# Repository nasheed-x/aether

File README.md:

# Aether: Flight Computer

## Overview

Aether is a multifunctional flight computer designed as an adaptable testbed for a variety of flight hardware and software components. The primary objective of this project is to evaluate external sensors and various algorithmic approaches, with a specific focus on sensor fusion techniques. These techniques aim to extract essential data regarding the rocket's states throughout its flight. The flight computer is equipped with the capability to interface with on-board rocket hardware, including deployment mechanisms.

## Key Features

- **Sensor Evaluation:** Aether serves as a platform for evaluating external sensors, with a particular emphasis on sensor fusion techniques.

- **Algorithmic Exploration:** The project explores various algorithmic approaches to extract crucial data about the rocket's states during its flight.

- **Hardware Interface:** The flight computer is designed to interface seamlessly with on-board rocket hardware, facilitating communication and control, especially with deployment mechanisms.

- **Dual Microcontroller Units:** Aether incorporates two microcontroller units (MCUs), each specialized for distinct tasks. One MCU is dedicated to data sampling, while the other focuses on communication with the ground station.

## Microcontrollers on Board

| Microcontroller         |
|-------------------------|
| STM32F405RGTx           |
| ESP32-S3-MINI-1U-N8     |

## Components on Board

| Component                                         | Interface |
|------------------------------------------------|-----------|
| TE MS8607 PHT Sensor                           | I2C       |
| DPS310 Precision Barometric Pressure and Altitude Sensor | I2C, SPI  |
| H3LIS331 Ultra High Range Triple-Axis Accelerometer | I2C, SPI  |
| LSM6DSO32 6-DoF Accelerometer and Gyroscope    | I2C, SPI  |
| Sensirion SHT45 Precision Temperature & Humidity Sensor | I2C       |
| SAM M10Q (GPS)                                       | I2C       |
| RFM 95 HCW (LoRa Transceiver)                                | SPI       |
| W25Q128JVSIQ (Flash)                           | SPI       |

## Project Link

View this project on [CADLAB.io](https://cadlab.io/project/27167) for additional details, documentation, and collaborative contributions.

Feel free to explore, contribute, and adapt Aether as needed for your specific flight hardware and software requirements.

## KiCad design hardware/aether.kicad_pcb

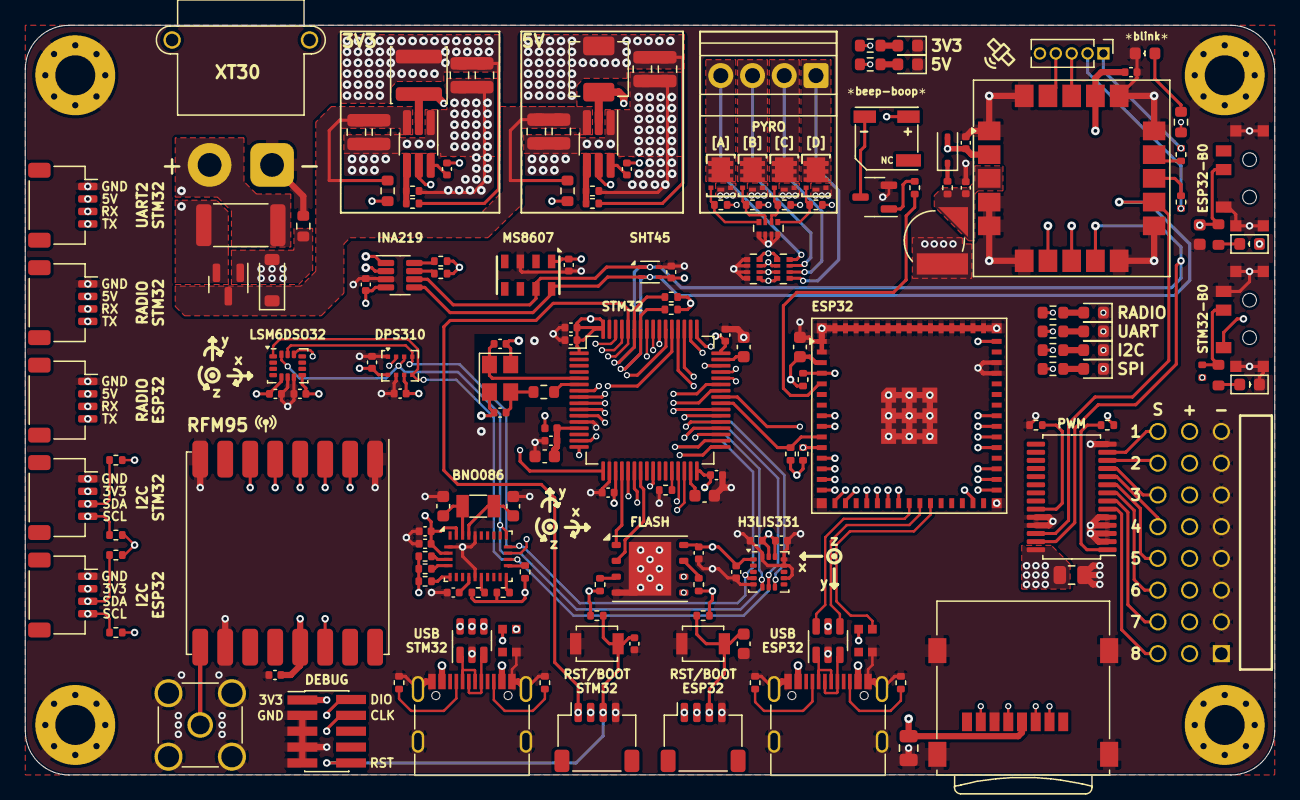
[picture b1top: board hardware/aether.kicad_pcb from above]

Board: 6 copper layers, 100.0 x 60.0 mm, 173 parts (0 on the bottom side), 147 nets.

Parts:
ANT1: Antenna_Shield; SMA_Amphenol_901-144_Vertical
BT1: Battery_Cell; SEIKO_ML414H_IV01E
BUZ1: FST-5030; BUZ-SMD_FST-5030
C1, C2: 2.2uF; C_0603_1608Metric
C3, C4, C5, C6, C7, C10, C12, C16, C17, C18, C19, C20, C21, C22, C23, C24, C26, C27, C28, C30, C31, C34, C39, C42, C43, C46, C47: 100nF; C_0402_1005Metric
C8, C9: 10pF; C_0402_1005Metric
C11, C13, C14: 1uF; C_0603_1608Metric
C15: 10uF; C_0603_1608Metric
C25, C29, C32, C33, C37, C38: 10uF; C_0805_2012Metric
C35, C36, C40, C41: 22uF; C_0805_2012Metric
C44, C45: 22pF; C_0603_1608Metric
D1: PULSE_LED; LED_0603_1608Metric
D2: 0.5A/40V/420mV; D_SOD-323
D3: FUXINSEMI DSK34; D_SOD-123
D4: RUBY RED; LED_0603_1608Metric
D5: ROYAL BLUE; LED_0603_1608Metric
D6: EMERALD GREEN; LED_0603_1608Metric
D7: ORANGE; LED_0603_1608Metric
ESP32-S3: ESP32-S3-MINI-1U; ESP32-S2-MINI-1U
ESPBOOT0: G; LED_0603_1608Metric
ESPRGB1: WS2812B-2020; LED_WS2812B-2020_PLCC4_2.0x2.0mm
ESP_B0: SS-3292S-L2-B; SW-SMD_SS-3292S-L2-B
ESP_RST1: SW_Push; SW_SPST_B3U-1000P
FB1: 600Ω; L_0402_1005Metric
G2: LOGO
GPS_IO1: Conn_01x05_Pin; PinHeader_1x05_P1.27mm_Vertical
H1, H2, H3, H4: MountingHole_Pad; MountingHole_3.2mm_M3_Pad_Via
HSE1: 25MHz; Crystal_SMD_Abracon_ABM8G-4Pin_3.2x2.5mm
I2C-ESP1, I2C-STM1: SM04B-SRSS-TB(LF)(SN); JST_SH_SM04B-SRSS-TB_1x04-1MP_P1.00mm_Horizontal
INA219: INA219AxDCN; SOT-23-8
L1: 4.7uH; L_Changjiang_FXL0420
L2: 3.3uH; L_Changjiang_FNR4030S
LED1, LED2: R; LED_0603_1608Metric
PCA9685: PCA9685PW; TSSOP-28_4.4x9.7mm_P0.65mm
PWM1: 24-Pin 8x3 Male Header - Angle; SAMTEC_TSW-108-08-T-T-RA
PYRO1: Screw_Terminal_01x04; TerminalBlock_Xinya_XY308-2.54-4P_1x04_P2.54mm_Horizontal
Q1: S8050_C2146; SOT-23-3
Q6: AO3401A; SOT-23
R1, R5, R13, R25, R26, R27, R28, R29, R30, R31, R32, R37, R40, R42, R43, R58, R59, R60, R61: 10k; R_0402_1005Metric
R2: 180; R_0402_1005Metric
R3: 620; R_0603_1608Metric
R4: 2.2K; R_0603_1608Metric
R6, R7, R16, R19, R20, R55: 5.1k; R_0402_1005Metric
R8, R9, R10, R11: 330; R_0402_1005Metric
R12, R23, R45, R46, R47, R48, R49, R50: 2.2k; R_0603_1608Metric
R14, R15, R33, R34, R56, R57: 4.7k; R_0402_1005Metric
R21, R22: 470; R_0402_1005Metric
R24: 3.3k; R_0402_1005Metric
R35, R38, R41: 100k; R_0603_1608Metric
R36: 54.9k; R_0402_1005Metric
R39: 33.2k; R_0402_1005Metric
R44: 0.01; R_2512_6332Metric
RFM95: RFM95W-915S2; HOPERF_RFM9XW_SMD
RN1: 10k; R_Array_Convex_4x0402
RN2: 47k; R_Array_Convex_4x0402
RN3: 220k; R_Array_Convex_4x0402
RST_BOOT_ESP1: SM04B-SRSS-TB(LF)(SN); JST_SH_SM04B-SRSS-TB_1x04-1MP_P1.00mm_Horizontal
RST_BOOT_STM1: SM04B-SRSS-TB(LF)(SN); JST_SH_SM04B-SRSS-TB_1x04-1MP_P1.00mm_Horizontal
SAM-M10Q1: SAM-M10Q-00B; ublox_SAM-M8Q
SD1: Micro_SD_Card; microSD_HC_Wuerth_693072010801
STM32F4: STM32F405RGTx; LQFP-64_10x10mm_P0.5mm
STMBOOT0: LED; LED_0603_1608Metric
STMRGB1: WS2812B-2020; LED_WS2812B-2020_PLCC4_2.0x2.0mm
STM_B0: SS-3292S-L2-B; SW-SMD_SS-3292S-L2-B
STM_RST1: SW_Push; SW_SPST_B3U-1000P
SWD1: Conn_02x05_Odd_Even; PinHeader_2x05_P1.27mm_Vertical_SMD
U1, U2: USBLC6-2SC6; SOT-23-6
U3, U7, U12, U14: SI5448DU-T1-GE3; SON_8DU-T1-GE3_VIS
U4: DPS310; XDCR_DPS310
U5: H3LIS331DL; LGA-16_3x3mm_P0.5mm_LayoutBorder3x5y
U6: LSM6DSO32TR; LGA-14_3x2.5mm_P0.5mm_LayoutBorder3x4y
U8: MS860702BA01-50; MS8607-02BA01
U9: SHT45-AD1B-R2; Sensirion_DFN-4_1.5x1.5mm_P0.8mm_SHT4x_NoCentralPad
U10, U11: TPS562201DDCR; TSOT-23-6_HandSoldering
U13: BNO086; LGA-28_5.2x3.8mm_P0.5mm
U15: W25Q128JVP; WSON-8-1EP_6x5mm_P1.27mm_EP3.4x4.3mm
UART1-RFD-ESP1, UART1-RFD-STM1, UART2-STM1: SM04B-SRSS-TB(LF)(SN); JST_SH_SM04B-SRSS-TB_1x04-1MP_P1.00mm_Horizontal
USB_ESP32: USB_C_Receptacle_USB2.0; USB_C_Receptacle_G-Switch_GT-USB-7010ASV
USB_STM32: USB_C_Receptacle_USB2.0; USB_C_Receptacle_G-Switch_GT-USB-7010ASV
XT30: XT30PW-M; AMASS_XT30PW-M_1x02_P2.50mm_Horizontal
Y1: 32.768kHz; Crystal_SMD_3215-2Pin_3.2x1.5mm

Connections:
3.3V: BUZ1.1 (+), C3.1, C4.1, C5.1, C6.1, C7.1, C15.1, C16.1, C17.1, C18.1, C19.1, C20.1, C21.1, C22.1, C24.1, C25.1, C26.1, C27.1, C28.1, C29.1, C30.1, C31.1, C40.1, C41.1, C42.1, C46.1, C47.1, D2.2 (A), ESP32-S3.3 (3V3), ESPBOOT0.2 (A), ESPRGB1.4 (VDD), FB1.2, I2C-ESP1.2, I2C-STM1.2, INA219.4 (VS), L2.2, PCA9685.28 (VDD), R13.2, R14.2, R15.2, R16.2, R25.1, R26.1, R28.2, R29.2, R30.2, R31.2, R32.2, R33.2, R34.2, R39.1, R42.2, R43.2, R46.1, R55.2, R56.2, R57.2, R58.1, R59.1, R60.1, R61.2, RFM95.13 (3.3V), RST_BOOT_ESP1.2, RST_BOOT_STM1.2, SAM-M10Q1.2 (V_IO), SAM-M10Q1.17 (VCC), SD1.4 (VDD), STM32F4.1 (VBAT), STM32F4.19 (VDD), STM32F4.32 (VDD), STM32F4.48 (VDD), STM32F4.64 (VDD), STMRGB1.4 (VDD), STM_B0.1, SWD1.1, U4.6 (VDDIO), U4.8 (VDD), U5.1 (VDD_IO), U5.14 (VDD), U5.15 (VDD), U6.5 (VDDIO), U6.8 (VDD), U8.1 (VDD), U9.3 (VDD), U13.3 (VDD), U13.28 (VDDIO), U15.8 (VCC)
5V: C35.1, C36.1, L1.2, PWM1.02, PWM1.05, PWM1.08, PWM1.11, PWM1.14, PWM1.17, PWM1.20, PWM1.23, R36.1, R45.1, UART1-RFD-ESP1.2, UART1-RFD-STM1.2, UART2-STM1.2
BNO086_CS: STM32F4.39 (PC8), U13.18 (~H_CS)
BNO086_MISO: SD1.3 (CMD), STM32F4.35 (PB14), U4.3 (SDI), U5.6 (SDA/SDI/SDO), U6.14 (SDA), U13.20 (H_SDA/H_MISO/TX)
BNO086_MOSI: SD1.7 (DAT0), STM32F4.36 (PB15), U4.5 (SDO), U5.7 (SDO/SA0), U6.1 (SDO/SA0), U13.17 (SA0/H_MOSI)
BNO086_RST: R61.1, U13.11 (~RST)
BNO086_SCK: SD1.5 (CLK), STM32F4.34 (PB13), U4.4 (SCK), U5.4 (SCL/SPC), U6.13 (SCL), U13.19 (H_SCL/SCK/RX)
BUZZ_IN: ESP32-S3.5 (IO1), R2.2
CROSS_I2C: ESP32-S3.36 (IO40), R49.2
CROSS_SPI: ESP32-S3.35 (IO39), R48.2
CROSS_UART: ESP32-S3.37 (IO41), R50.2
DPS310_CSB: STM32F4.33 (PB12), U4.2 (~CSB)
ESP32-EN: C14.1, ESP32-S3.45 (EN), ESP_RST1.2, R16.1, RST_BOOT_ESP1.3
ESP32-GPIO0: C13.1, ESP32-S3.4 (IO0), ESP_B0.2, R12.1, R13.1, RST_BOOT_ESP1.1
ESP32-I2C1_SCL: ESP32-S3.9 (IO5), I2C-ESP1.4, R32.1
ESP32-I2C1_SDA: ESP32-S3.8 (IO4), I2C-ESP1.3, R31.1
ESP32-I2C2_SCL: ESP32-S3.11 (IO7), R15.1, STM32F4.41 (PA8)
ESP32-I2C2_SDA: ESP32-S3.10 (IO6), R14.1, STM32F4.40 (PC9)
ESP32-RGB_IN: ESP32-S3.25 (IO21), ESPRGB1.3 (DIN)
ESP32-RX1: ESP32-S3.22 (IO18), UART1-RFD-ESP1.3
ESP32-RX2: ESP32-S3.20 (IO16), STM32F4.51 (PC10)
ESP32-SPI1_CS0: ESP32-S3.14 (IO10), RFM95.5 (NSS)
ESP32-SPI1_MISO: ESP32-S3.17 (IO13), RFM95.2 (MISO)
ESP32-SPI1_MOSI: ESP32-S3.15 (IO11), RFM95.3 (MOSI)
ESP32-SPI1_SCK: ESP32-S3.16 (IO12), RFM95.4 (SCK)
ESP32-SPI2_CS0: ESP32-S3.29 (IO34), STM32F4.50 (PA15)
ESP32-SPI2_MISO: ESP32-S3.33 (IO37), STM32F4.56 (PB4)
ESP32-SPI2_MOSI: ESP32-S3.31 (IO35), STM32F4.57 (PB5)
ESP32-SPI2_SCK: ESP32-S3.32 (IO36), STM32F4.55 (PB3)
ESP32-TX1: ESP32-S3.21 (IO17), UART1-RFD-ESP1.4
ESP32-TX2: ESP32-S3.19 (IO15), STM32F4.52 (PC11)
ESP32-USB_D+: ESP32-S3.24 (USB_D+), U2.4 (I/O2)
ESP32-USB_D-: ESP32-S3.23 (USB_D-), U2.6 (I/O1)
F405_VDDA: C10.1, C11.1, FB1.1, STM32F4.13 (VDDA)
FLASH_CLK: STM32F4.21 (PA5), U15.6 (CLK)
FLASH_CS: STM32F4.20 (PA4), U15.1 (~CS)
FLASH_HOLD: R26.2, U15.7 (~HOLD/~RESET/IO_{3})
FLASH_SDI: STM32F4.22 (PA6), U15.5 (DI/IO_{0})
FLASH_SDO: STM32F4.23 (PA7), U15.2 (DO/IO_{1})
FLASH_WP: R25.2, U15.3 (~WP/IO_{2})
GND: ANT1.2 (Shield), BT1.2 (-), C1.2, C2.2, C3.2, C4.2, C5.2, C6.2, C7.2, C8.1, C9.2, C10.2, C11.2, C12.2, C13.2, C14.2, C15.2, C16.2, C17.2, C18.2, C19.2, C20.2, C21.2, C22.2, C23.2, C24.2, C25.2, C26.2, C27.2, C28.2, C29.2, C30.2, C31.2, C32.2, C33.2, C35.2, C36.2, C37.2, C38.2, C40.2, C41.2, C42.2, C43.2, C44.2, C45.2, C46.2, C47.2, D1.1 (K), D4.1 (K), D5.1 (K), D6.1 (K), D7.1 (K), ESP32-S3.1 (GND), ESP32-S3.2 (GND), ESP32-S3.42 (GND), ESP32-S3.43 (GND), ESP32-S3.46 (GND), ESP32-S3.47 (GND), ESP32-S3.48 (GND), ESP32-S3.49 (GND), ESP32-S3.50 (GND), ESP32-S3.51 (GND), ESP32-S3.52 (GND), ESP32-S3.53 (GND), ESP32-S3.54 (GND), ESP32-S3.55 (GND), ESP32-S3.56 (GND), ESP32-S3.57 (GND), ESP32-S3.58 (GND), ESP32-S3.59 (GND), ESP32-S3.60 (GND), ESP32-S3.61 (GND), ESP32-S3.62 (GND), ESP32-S3.63 (GND), ESP32-S3.64 (GND), ESP32-S3.65 (GND), ESPRGB1.2 (VSS), ESP_B0.1, ESP_B0.EH, ESP_RST1.1, H1.1, H2.1, H3.1, H4.1, HSE1.2, HSE1.4, I2C-ESP1.1, I2C-STM1.1, INA219.3 (GND), LED1.1 (K), LED2.1 (K), PCA9685.2 (A1), PCA9685.3 (A2), PCA9685.4 (A3), PCA9685.5 (A4), PCA9685.14 (VSS), PCA9685.24 (A5), PCA9685.25 (EXTCLK), PWM1.01, PWM1.04, PWM1.07, PWM1.10, PWM1.13, PWM1.16, PWM1.19, PWM1.22, Q1.2 (E), R1.1, R6.1, R7.2, R19.1, R20.2, R27.2, R37.2, R40.2, R41.2, RFM95.1 (GND), RFM95.8 (GND), RFM95.10 (GND), RN1.5 (R4.2), RN1.6 (R3.2), RN1.7 (R2.2), RN1.8 (R1.2), RN2.1 (R1.1), RN2.2 (R2.1), RN2.3 (R3.1), RN2.4 (R4.1), RST_BOOT_ESP1.4, RST_BOOT_STM1.4, SAM-M10Q1.1 (GND), SAM-M10Q1.4 (GND), SAM-M10Q1.5 (GND), SAM-M10Q1.6 (GND), SAM-M10Q1.10 (GND), SAM-M10Q1.11 (GND), SAM-M10Q1.15 (GND), SAM-M10Q1.16 (GND), SAM-M10Q1.20 (GND), SD1.6 (VSS), SD1.9 (SHIELD), STM32F4.12 (VSSA), STM32F4.18 (VSS), STM32F4.63 (VSS), STMBOOT0.1 (K), STMRGB1.2 (VSS), STM_B0.3, STM_B0.EH, STM_RST1.1, SWD1.3, SWD1.5, SWD1.7, SWD1.9, U1.2 (GND), U2.2 (GND), U3.5 (S), U3.9 (S), U4.1 (GND), U4.7 (GND), U5.5 (GND), U5.10 (GND), U5.12 (GND), U5.13 (GND), U5.16 (GND), U6.6 (GND), U6.7 (GND), U7.5 (S), U7.9 (S), U8.3 (GND), U9.4 (VSS), U10.1 (GND), U11.1 (GND), U12.5 (S), U12.9 (S), U13.2 (GND), U13.10 (CLKSEL0), U13.25 (GNDIO), U14.5 (S), U14.9 (S), U15.4 (GND), U15.9 (EP), UART1-RFD-ESP1.1, UART1-RFD-STM1.1, UART2-STM1.1, USB_ESP32.A1 (GND), USB_ESP32.A12 (GND), USB_ESP32.B1 (GND), USB_ESP32.B12 (GND), USB_ESP32.S1 (SHIELD), USB_STM32.A1 (GND), USB_STM32.A12 (GND), USB_STM32.B1 (GND), USB_STM32.B12 (GND), USB_STM32.S1 (SHIELD), XT30.1 (N)
GPS_INT: GPS_IO1.4, SAM-M10Q1.19 (EXTINT)
GPS_RST: GPS_IO1.3, SAM-M10Q1.18 (~RESET)
GPS_RX: GPS_IO1.1, R22.2
GPS_SAFE: GPS_IO1.5, SAM-M10Q1.8 (~SAFEBOOT)
GPS_SCL: INA219.5 (SCL), PCA9685.26 (SCL), R34.1, SAM-M10Q1.12 (SCL), STM32F4.58 (PB6), U8.8 (SCL), U9.2 (SCL)
GPS_SDA: INA219.6 (SDA), PCA9685.27 (SDA), R33.1, SAM-M10Q1.9 (SDA), STM32F4.59 (PB7), U8.7 (SDA), U9.1 (SDA)
GPS_TX: GPS_IO1.2, R21.1
GPS_VBCKP: BT1.1 (+), C23.1, R24.1, SAM-M10Q1.3 (V_BCKP)
H3LIS331DL_CS: STM32F4.37 (PC6), U5.8 (CS)
INA219_IN+: INA219.1 (IN+), R44.1, XT30.2
INA219_IN-: INA219.2 (IN-), Q6.2 (D), R44.2
LSM6DSO32TR_CS: STM32F4.25 (PC5), U6.12 (CS)
unnamed: C9.1, HSE1.3, R3.2
unnamed: D1.2 (A), R23.1
unnamed: D2.1 (K), R24.2
unnamed: D4.2 (A), R47.1
unnamed: D5.2 (A), R48.1
unnamed: D6.2 (A), R49.1
unnamed: D7.2 (A), R50.1
unnamed: ESPBOOT0.1 (K), R12.2
unnamed: INA219.7 (A0), R43.1
unnamed: INA219.8 (A1), R42.1
unnamed: LED1.2 (A), R45.2
unnamed: LED2.2 (A), R46.2
unnamed: PCA9685.1 (A0), R28.1
unnamed: PCA9685.23 (~OE), R27.1
unnamed: Q1.1 (B), R2.1
unnamed: BUZ1.2, Q1.3 (C)
unnamed: R4.2, R5.2, STM_B0.2
unnamed: R11.1, RN1.1 (R1.1), U3.4 (G)
unnamed: R10.1, RN1.2 (R2.1), U7.4 (G)
unnamed: R9.1, RN1.3 (R3.1), U12.4 (G)
unnamed: R8.1, RN1.4 (R4.1), U14.4 (G)
unnamed: R22.1, SAM-M10Q1.14 (RXD)
unnamed: R21.2, SAM-M10Q1.13 (TXD)
unnamed: R1.2, STM32F4.28 (PB2)
unnamed: C1.1, STM32F4.31 (VCAP_1)
unnamed: C2.1, STM32F4.47 (VCAP_2)
unnamed: R4.1, STMBOOT0.2 (A)
unnamed: R35.2, U10.5 (EN)
unnamed: C34.2, L1.1, U10.2 (SW)
unnamed: C34.1, U10.6 (VBST)
unnamed: R36.2, R37.1, U10.4 (VFB)
unnamed: R38.2, U11.5 (EN)
unnamed: C39.2, L2.1, U11.2 (SW)
unnamed: C39.1, U11.6 (VBST)
unnamed: R39.2, R40.1, U11.4 (VFB)
unnamed: C43.1, U13.9 (CAP)
unnamed: R56.1, U13.15 (ENV_SCL)
unnamed: R57.1, U13.16 (ENV_SDA)
unnamed: R59.2, U13.6 (PS0/WAKE)
unnamed: R58.2, U13.5 (PS1)
unnamed: C44.1, U13.27 (XIN32), Y1.2
unnamed: C45.1, U13.26 (XOUT32/CLKSEL1), Y1.1
unnamed: R60.2, U13.4 (~BOOT)
unnamed: R19.2, USB_ESP32.A5 (CC1)
unnamed: R20.1, USB_ESP32.B5 (CC2)
unnamed: R6.2, USB_STM32.A5 (CC1)
unnamed: R7.1, USB_STM32.B5 (CC2)
PULSE: R23.2, SAM-M10Q1.7 (TIMEPULSE)
PWM0: PCA9685.13 (LED7), PWM1.24
PWM1: PCA9685.12 (LED6), PWM1.21
PWM2: PCA9685.11 (LED5), PWM1.18
PWM3: PCA9685.10 (LED4), PWM1.15
PWM4: PCA9685.9 (LED3), PWM1.12
PWM5: PCA9685.8 (LED2), PWM1.09
PWM6: PCA9685.7 (LED1), PWM1.06
PWM7: PCA9685.6 (LED0), PWM1.03
PYRO-TERM_A: PYRO1.4, RN3.8 (R1.2), U14.1 (D)
PYRO-TERM_B: PYRO1.3, RN3.7 (R2.2), U12.1 (D)
PYRO-TERM_C: PYRO1.2, RN3.6 (R3.2), U7.1 (D)
PYRO-TERM_D: PYRO1.1, RN3.5 (R4.2), U3.1 (D)
PYRO_A: R8.2, STM32F4.62 (PB9)
PYRO_B: R9.2, STM32F4.61 (PB8)
PYRO_C: R10.2, STM32F4.54 (PD2)
PYRO_D: R11.2, STM32F4.53 (PC12)
RFD_900: ESP32-S3.38 (IO42), R47.2
RFM95W_ANT: ANT1.1 (A), RFM95.9 (ANT)
RFM95W_DI0: ESP32-S3.13 (IO9), RFM95.14 (DIO0)
RFM95W_RST: ESP32-S3.12 (IO8), RFM95.6 (RESET)
SD_CS: SD1.2 (DAT3/CD), STM32F4.38 (PC7)
STM32-BOOT0: R5.1, RST_BOOT_STM1.1, STM32F4.60 (BOOT0)
STM32-HSE_IN: C8.2, HSE1.1, STM32F4.5 (PH0)
STM32-HSE_OUT: R3.1, STM32F4.6 (PH1)
STM32-I2C2_SCL: I2C-STM1.4, R30.1, STM32F4.29 (PB10)
STM32-I2C2_SDA: I2C-STM1.3, R29.1, STM32F4.30 (PB11)
STM32-NRST: C12.1, R55.1, RST_BOOT_STM1.3, STM32F4.7 (NRST), STM_RST1.2, SWD1.10
STM32-RGB_IN: STM32F4.15 (PA1), STMRGB1.3 (DIN)
STM32-SWCLK: STM32F4.49 (PA14), SWD1.4
STM32-SWDIO: STM32F4.46 (PA13), SWD1.2
STM32-UART1_RX: STM32F4.43 (PA10), UART1-RFD-STM1.3
STM32-UART1_TX: STM32F4.42 (PA9), UART1-RFD-STM1.4
STM32-UART2_RX: STM32F4.17 (PA3), UART2-STM1.3
STM32-UART2_TX: STM32F4.16 (PA2), UART2-STM1.4
STM32_USB_D+: STM32F4.45 (PA12), U1.4 (I/O2)
STM32_USB_D-: STM32F4.44 (PA11), U1.6 (I/O1)
USB1_D+: U1.3 (I/O2), USB_STM32.A6 (D+), USB_STM32.B6 (D+)
USB1_D-: U1.1 (I/O1), USB_STM32.A7 (D-), USB_STM32.B7 (D-)
USB2_D+: U2.3 (I/O2), USB_ESP32.A6 (D+), USB_ESP32.B6 (D+)
USB2_D-: U2.1 (I/O1), USB_ESP32.A7 (D-), USB_ESP32.B7 (D-)
V-TERM_A: RN2.8 (R1.2), RN3.1 (R1.1), STM32F4.8 (PC0)
V-TERM_B: RN2.7 (R2.2), RN3.2 (R2.1), STM32F4.9 (PC1)
V-TERM_C: RN2.6 (R3.2), RN3.3 (R3.1), STM32F4.10 (PC2)
V-TERM_D: RN2.5 (R4.2), RN3.4 (R4.1), STM32F4.11 (PC3)
VBUS: D3.2 (A), Q6.1 (G), R41.1, U1.5 (VBUS), U2.5 (VBUS), USB_ESP32.A4 (VBUS), USB_ESP32.A9 (VBUS), USB_ESP32.B4 (VBUS), USB_ESP32.B9 (VBUS), USB_STM32.A4 (VBUS), USB_STM32.A9 (VBUS), USB_STM32.B4 (VBUS), USB_STM32.B9 (VBUS)
VIN: C32.1, C33.1, C37.1, C38.1, D3.1 (K), Q6.3 (S), R35.1, R38.1, U10.3 (VIN), U11.3 (VIN)

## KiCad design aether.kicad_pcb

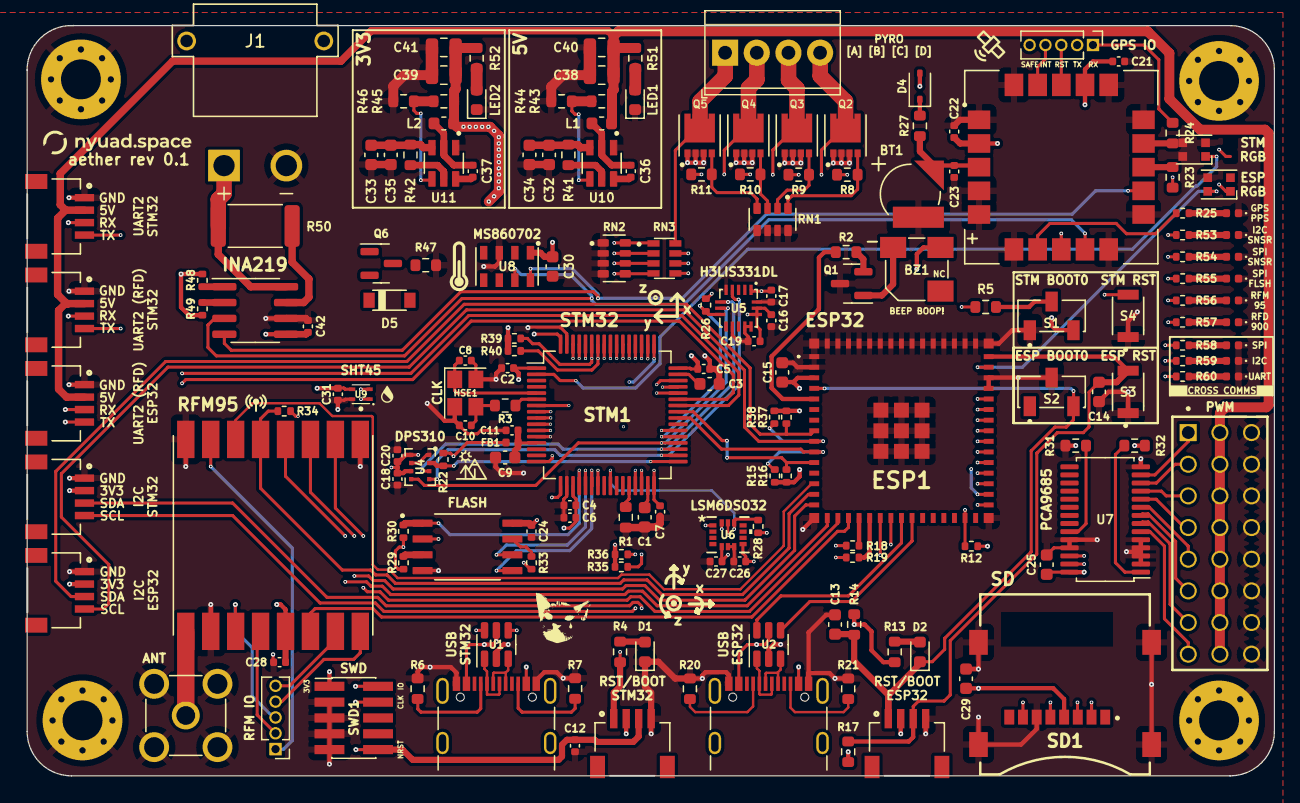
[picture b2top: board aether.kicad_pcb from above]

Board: 4 copper layers, 100.1 x 60.2 mm, 171 parts (0 on the bottom side), 152 nets.

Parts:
ANT1: 5-1814832-1; TE_5-1814832-1
BT1: Battery_Cell; SEIKO_ML414H_IV01E
BZ1: CSS-0575A-SMT; CUI_CSS-0575A-SMT
C1, C3: 2.2uF; C_0603_1608Metric
C2, C4, C5, C6, C7, C11, C12, C16, C17, C18, C19, C20, C21, C22, C23, C26, C27, C28, C31, C36, C37, C42: 100nF; C_0402_1005Metric
C8, C10: 10pF; C_0402_1005Metric
C9, C13, C14: 1uF; C_0603_1608Metric
C15, C25, C29, C32, C33, C34, C35: 10uF; C_0603_1608Metric
C24: 10uF; C_0402_1005Metric
C30: 220nF; C_0603_1608Metric
C38, C39, C40, C41: 22uF; C_0805_2012Metric
D1: LED; LED_0603_1608Metric
D2: G; LED_0603_1608Metric
D3, D6, D7, D8, D9, D10, D11, D12, D13: LED; LED_0402_1005Metric
D4: 0.5A/40V/420mV; D_SOD-323
D5: B5819W-TP; SOD3716X135N
ESP1: ESP32-S3-MINI-1U-N8; ESP32S3MINI1UN8
FB1: 600Ω; L_0402_1005Metric
HSE1: 25MHz; Crystal_SMD_Abracon_ABM8G-4Pin_3.2x2.5mm
I2C-ESP1, I2C-STM1: SM04B-SRSS-TB(LF)(SN); JST_SM04B-SRSS-TB(LF)(SN)
J1: XT30PW-M; AMASS_XT30PW-M
J2: Screw_Terminal_01x04; TerminalBlock_TE_282834-4_1x04_P2.54mm_Horizontal
L1, L2: 3.9uH; L_0603_1608Metric
LED1, LED2: R; LED_0603_1608Metric
PWM1: TSW-108-07-G-T; SAMTEC_TSW-108-07-G-T
Q1: NPN; SOT-23
Q2, Q3, Q4, Q5: CSD17575Q3; TRANS_CSD17308Q3
Q6: PNP; SOT-23
R1, R5, R14, R17, R31, R32, R44, R46: 10k; R_0603_1608Metric
R2: 1k; R_0603_1608Metric
R3: 620; R_0603_1608Metric
R4, R13: R; R_0603_1608Metric
R6, R7, R20, R21: 5.1k; R_0603_1608Metric
R8, R9, R10, R11: 330; R_0603_1608Metric
R12, R22, R26, R28, R29, R30, R33, R34, R35, R36, R37, R38, R48, R49: 10k; R_0402_1005Metric
R15, R16, R39, R40: 4.7k; R_0402_1005Metric
R18, R19: 10; R_0402_1005Metric
R23, R24: 470; R_0603_1608Metric
R25, R53, R54, R55, R56, R57, R58, R59, R60: 2.2k; R_0402_1005Metric
R27: 3.3k; R_0603_1608Metric
R41, R42, R47: 100k; R_0603_1608Metric
R43: 54.9k; R_0603_1608Metric
R45: 33.2k; R_0603_1608Metric
R50: 0.01; R_2512_6332Metric
R51: 560; R_0603_1608Metric
R52: 240; R_0603_1608Metric
RFM1: RFM95W-915S2; XCVR_RFM95W-915S2
RFM2, RFM3: Conn_01x05_Pin; PinHeader_1x05_P1.27mm_Vertical
RGB1, RGB2: WS2812B-2020; LED_WS2812B-2020_PLCC4_2.0x2.0mm
RN1: 10k; RESCAXE80P320X160X70-8N
RN2: 47k; RESCAXE80P320X160X70-8N
RN3: 270k; RESCAV80P320X160X70-8N
RST-BOOT-ESP1: SM04B-SRSS-TB(LF)(SN); JST_SM04B-SRSS-TB(LF)(SN)
RST-BOOT-STM1: SM04B-SRSS-TB(LF)(SN); JST_SM04B-SRSS-TB(LF)(SN)
S1, S2: CJS-1200TA; SW_CJS-1200TA
S3, S4: B3U-1000P; SW_B3U-1000P
SD1: MEM2067-02-180-00-A_REVB; GCT_MEM2067-02-180-00-A_REVB
STM1: STM32F405RGTx; LQFP-64_10x10mm_P0.5mm
SWD1: Conn_02x05_Odd_Even; PinHeader_2x05_P1.27mm_Vertical_SMD
U1, U2: USBLC6-2SC6; SOT-23-6
U3: SAM-M10Q-00B; XCVR_SAM-M10Q-00B
U4: DPS310; XDCR_DPS310
U5: H3LIS331DL; QFN300X300X100-16N
U6: LSM6DSO32TR; LGA-14L_2P5X3X0P83_STM
U7: PCA9685PW; TSSOP-28_4.4x9.7mm_P0.65mm
U8: MS860702BA01-50; TE_MS860702BA01-50
U9: SHT45-AD1B-R2; SHT4X
U10, U11: TPS562201DDCR; SOT95P280X110-6N
U12: INA219AxD; SOIC-8_3.9x4.9mm_P1.27mm
UART1-RFD-ESP1, UART1-RFD-STM1, UART2-STM1: SM04B-SRSS-TB(LF)(SN); JST_SM04B-SRSS-TB(LF)(SN)
USB1, USB2: USB_C_Receptacle_USB2.0; USB_C_Receptacle_GCT_USB4105-xx-A_16P_TopMnt_Horizontal
W25Q1: W25Q128JVSIQ; SOIC127P790X216-8N

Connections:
3.3V: BZ1.1, C2.1, C4.1, C5.1, C6.1, C7.1, C15.1, C16.1, C17.1, C18.1, C19.1, C20.1, C21.1, C22.1, C24.1, C25.1, C26.1, C27.1, C28.1, C29.1, C30.1, C31.1, C39.1, C41.1, C42.1, D4.2 (A), ESP1.3 (3V3), FB1.2, I2C-ESP1.2, I2C-STM1.2, L2.2, R12.1, R13.2, R14.2, R15.2, R16.2, R17.2, R22.1, R26.1, R28.1, R29.1, R30.1, R32.2, R33.1, R34.1, R35.2, R36.2, R37.2, R38.2, R39.2, R40.2, R45.1, R48.2, R49.2, R52.1, RFM1.13 (3.3V), RGB1.1 (VDD), RGB2.1 (VDD), RST-BOOT-ESP1.2, RST-BOOT-STM1.2, S1.3, SD1.4 (VDD), STM1.1 (VBAT), STM1.19 (VDD), STM1.32 (VDD), STM1.48 (VDD), STM1.64 (VDD), SWD1.1, U3.2 (V_IO), U3.17 (VCC), U4.6 (VDDIO), U4.8 (VDD), U5.1 (VDD_IO), U5.14 (VDD), U5.15 (VDD), U6.5 (VDDIO), U6.8 (VDD), U7.28 (VDD), U8.1 (VDD), U9.3 (VDD), U12.5 (VS), W25Q1.8 (VCC)
5V: C38.1, C40.1, L1.2, PWM1.02, PWM1.05, PWM1.08, PWM1.11, PWM1.14, PWM1.17, PWM1.20, PWM1.23, R43.1, R51.1, UART1-RFD-ESP1.2, UART1-RFD-STM1.2, UART2-STM1.2
BUZZ_IN: ESP1.5 (IO1), R2.2
CROSS_I2C: ESP1.35 (IO39), R59.2
CROSS_SPI: ESP1.36 (IO40), R58.2
CROSS_UART: ESP1.34 (IO38), R60.2
DPS310_CSB: R22.2, STM1.33 (PB12), U4.2 (~CSB)
DPS310_SCK: SD1.5 (CLK), STM1.34 (PB13), U4.4 (SCK), U5.4 (SCL/SPC), U6.13 (SCL)
DPS310_SDI/SDA: SD1.3 (CMD), STM1.35 (PB14), U4.3 (SDI), U5.6 (SDA/SDI/SDO), U6.14 (SDA)
DPS310_SDO: SD1.7 (DAT0), STM1.36 (PB15), U4.5 (SDO), U5.7 (SDO/SA0), U6.1 (SDO/SA0)
ESP32-EN: C14.1, ESP1.45 (EN), R17.1, RST-BOOT-ESP1.3, S3.2
ESP32-GPIO0: C13.1, D2.1 (K), ESP1.4 (IO0), R14.1, RST-BOOT-ESP1.1, S2.3
ESP32-I2C1_SCL: ESP1.9 (IO5), I2C-ESP1.4, R38.1
ESP32-I2C1_SDA: ESP1.8 (IO4), I2C-ESP1.3, R37.1
ESP32-I2C2_SCL: ESP1.11 (IO7), R16.1, STM1.41 (PA8)
ESP32-I2C2_SDA: ESP1.10 (IO6), R15.1, STM1.40 (PC9)
ESP32-RGB_IN: ESP1.44 (IO46), RGB2.4 (DIN)
ESP32-RX1: ESP1.22 (IO18), UART1-RFD-ESP1.3
ESP32-RX2: ESP1.20 (IO16), R19.2
ESP32-SPI1_CS0: ESP1.14 (IO10), R34.2, RFM1.5 (NSS)
ESP32-SPI1_MISO: ESP1.17 (IO13), RFM1.2 (MISO)
ESP32-SPI1_MOSI: ESP1.15 (IO11), RFM1.3 (MOSI)
ESP32-SPI1_SCK: ESP1.16 (IO12), RFM1.4 (SCK)
ESP32-SPI2_CS0: ESP1.29 (IO34), R12.2, STM1.50 (PA15)
ESP32-SPI2_MISO: ESP1.33 (IO37), STM1.56 (PB4)
ESP32-SPI2_MOSI: ESP1.31 (IO35), STM1.57 (PB5)
ESP32-SPI2_SCK: ESP1.32 (IO36), STM1.55 (PB3)
ESP32-TX1: ESP1.21 (IO17), UART1-RFD-ESP1.4
ESP32-TX2: ESP1.19 (IO15), R18.2
ESP32-USB_D+: ESP1.24 (IO20), U2.4 (I/O2)
ESP32-USB_D-: ESP1.23 (IO19), U2.6 (I/O1)
F405_VDDA: C9.1, C11.1, FB1.1, STM1.13 (VDDA)
FLASH_CLK: STM1.21 (PA5), W25Q1.6 (CLK)
FLASH_CS: R30.2, STM1.20 (PA4), W25Q1.1 (/CS)
FLASH_HOLD: R33.2, W25Q1.7 (/HOLD/RESET(IO3))
FLASH_SDI: STM1.22 (PA6), W25Q1.5 (DI(IO0))
FLASH_SDO: STM1.23 (PA7), W25Q1.2 (DO(IO1))
FLASH_WP: R29.2, W25Q1.3 (/WP(IO2))
GND: ANT1.2, ANT1.3 (2), ANT1.4 (2), ANT1.5 (2), BT1.2 (-), C1.2, C2.2, C3.2, C4.2, C5.2, C6.2, C7.2, C8.1, C9.2, C10.2, C11.2, C12.2, C13.2, C14.2, C15.2, C16.2, C17.2, C18.2, C19.2, C20.2, C21.2, C22.2, C23.2, C24.2, C25.2, C26.2, C27.2, C28.2, C29.2, C30.2, C31.2, C32.2, C33.2, C34.2, C35.2, C38.2, C39.2, C40.2, C41.2, C42.2, D1.1 (K), D3.1 (K), D6.1 (K), D7.1 (K), D8.1 (K), D9.1 (K), D10.1 (K), D11.1 (K), D12.1 (K), D13.1 (K), ESP1.1 (GND), ESP1.2 (GND), ESP1.42 (GND), ESP1.43 (GND), ESP1.46 (GND), ESP1.47 (GND), ESP1.48 (GND), ESP1.49 (GND), ESP1.50 (GND), ESP1.51 (GND), ESP1.52 (GND), ESP1.53 (GND), ESP1.54 (GND), ESP1.55 (GND), ESP1.56 (GND), ESP1.57 (GND), ESP1.58 (GND), ESP1.59 (GND), ESP1.60 (GND), ESP1.61 (GND), ESP1.62 (GND), ESP1.63 (GND), ESP1.64 (GND), ESP1.65 (GND), ESP1.66 (GND), ESP1.67 (GND), ESP1.68 (GND), ESP1.69 (GND), ESP1.70 (GND), ESP1.71 (GND), ESP1.72 (GND), ESP1.73 (GND), HSE1.2, HSE1.4, I2C-ESP1.1, I2C-STM1.1, J1.N, LED1.1 (K), LED2.1 (K), PWM1.03, PWM1.06, PWM1.09, PWM1.12, PWM1.15, PWM1.18, PWM1.21, PWM1.24, Q1.3 (E), Q2.1 (S), Q2.2 (S), Q2.3 (S), Q3.1 (S), Q3.2 (S), Q3.3 (S), Q4.1 (S), Q4.2 (S), Q4.3 (S), Q5.1 (S), Q5.2 (S), Q5.3 (S), R1.1, R6.1, R7.2, R20.1, R21.2, R31.2, R44.2, R46.2, R47.2, RFM1.1 (GND), RFM1.8 (GND), RFM1.10 (GND), RGB1.3 (VSS), RGB2.3 (VSS), RN1.5 (R4.2), RN1.6 (R3.2), RN1.7 (R2.2), RN1.8 (R1.2), RN2.1 (R1.1), RN2.2 (R2.1), RN2.3 (R3.1), RN2.4 (R4.1), RST-BOOT-ESP1.4, RST-BOOT-STM1.4, S1.1, S2.2, S3.1, S4.1, SD1.6 (VSS), SD1.9 (SHIELD), SD1.10 (SHIELD), SD1.11 (SHIELD), SD1.12 (SHIELD), STM1.12 (VSSA), STM1.18 (VSS), STM1.63 (VSS), SWD1.3, SWD1.5, SWD1.7, SWD1.9, U1.2 (GND), U2.2 (GND), U3.1 (GND), U3.4 (GND), U3.5 (GND), U3.6 (GND), U3.10 (GND), U3.11 (GND), U3.15 (GND), U3.16 (GND), U3.20 (GND), U4.1 (GND), U4.7 (GND), U5.5 (GND), U5.10 (GND), U5.12 (GND), U5.13 (GND), U5.16 (GND), U6.6 (GND), U6.7 (GND), U7.2 (A1), U7.3 (A2), U7.4 (A3), U7.5 (A4), U7.14 (VSS), U7.24 (A5), U7.25 (EXTCLK), U8.3 (GND), U9.4 (VSS), U10.1 (GND), U11.1 (GND), U12.6 (GND), UART1-RFD-ESP1.1, UART1-RFD-STM1.1, UART2-STM1.1, USB1.A1 (GND), USB1.A12 (GND), USB1.B1 (GND), USB1.B12 (GND), USB2.A1 (GND), USB2.A12 (GND), USB2.B1 (GND), USB2.B12 (GND), W25Q1.4 (GND)
GPS_INT: RFM3.4, U3.19 (EXTINT)
GPS_RST: RFM3.3, U3.18 (~RESET)
GPS_RX: R24.2, RFM3.1
GPS_SAFE: RFM3.5, U3.8 (~SAFEBOOT)
GPS_SCL: R40.1, STM1.58 (PB6), U3.12 (SCL), U7.26 (SCL), U8.8 (SCL), U9.2 (SCL), U12.4 (SCL)
GPS_SDA: R39.1, STM1.59 (PB7), U3.9 (SDA), U7.27 (SDA), U8.7 (SDA), U9.1 (SDA), U12.3 (SDA)
GPS_TX: R23.1, RFM3.2
GPS_VBCKP: BT1.1 (+), C23.1, R27.1, U3.3 (V_BCKP)
H3LIS331DL_CS: R26.2, STM1.37 (PC6), U5.8 (CS)
I2C-1_STM32: ESP1.41 (IO45), R53.2
INA219_IN+: J1.P, R50.1, U12.8 (IN+)
INA219_IN-: Q6.1 (C), R50.2, U12.7 (IN-)
LSM6DSO32TR_CS: R28.2, STM1.25 (PC5), U6.12 (CS)
unnamed: C10.1, HSE1.3, R3.2
unnamed: D1.2 (A), R4.1
unnamed: D2.2 (A), R13.1
unnamed: D3.2 (A), R25.1
unnamed: D4.1 (K), R27.2
unnamed: D6.2 (A), R53.1
unnamed: D7.2 (A), R54.1
unnamed: D8.2 (A), R55.1
unnamed: D9.2 (A), R56.1
unnamed: D10.2 (A), R57.1
unnamed: D11.2 (A), R58.1
unnamed: D12.2 (A), R59.1
unnamed: D13.2 (A), R60.1
unnamed: LED1.2 (A), R51.2
unnamed: LED2.2 (A), R52.2
unnamed: Q1.2 (B), R2.1
unnamed: BZ1.2, Q1.1 (C)
unnamed: Q2.4 (G), R8.1, RN1.1 (R1.1)
unnamed: Q3.4 (G), R9.1, RN1.2 (R2.1)
unnamed: Q4.4 (G), R10.1, RN1.3 (R3.1)
unnamed: Q5.4 (G), R11.1, RN1.4 (R4.1)
unnamed: R5.2, S1.2
unnamed: R1.2, STM1.28 (PB2)
unnamed: C1.1, STM1.31 (VCAP_1)
unnamed: C3.1, STM1.47 (VCAP_2)
unnamed: R24.1, U3.14 (RXD)
unnamed: R23.2, U3.13 (TXD)
unnamed: R32.1, U7.1 (A0)
unnamed: R31.1, U7.23 (~OE)
unnamed: R41.2, U10.5 (EN)
unnamed: C36.2, L1.1, U10.2 (SW)
unnamed: C36.1, U10.6 (VBST)
unnamed: R43.2, R44.1, U10.4 (VFB)
unnamed: R42.2, U11.5 (EN)
unnamed: C37.2, L2.1, U11.2 (SW)
unnamed: C37.1, U11.6 (VBST)
unnamed: R45.2, R46.1, U11.4 (VFB)
unnamed: R49.1, U12.2 (A0)
unnamed: R48.1, U12.1 (A1)
unnamed: R6.2, USB1.A5 (CC1)
unnamed: R7.1, USB1.B5 (CC2)
unnamed: R20.2, USB2.A5 (CC1)
unnamed: R21.1, USB2.B5 (CC2)
PULSE: R25.2, U3.7 (TIMEPULSE)
PWM0: PWM1.01, U7.13 (LED7)
PWM1: PWM1.04, U7.12 (LED6)
PWM2: PWM1.07, U7.11 (LED5)
PWM3: PWM1.10, U7.10 (LED4)
PWM4: PWM1.13, U7.9 (LED3)
PWM5: PWM1.16, U7.8 (LED2)
PWM6: PWM1.19, U7.7 (LED1)
PWM7: PWM1.22, U7.6 (LED0)
PYRO-TERM_A: J2.1, Q5.5-8, RN3.8 (R1.2)
PYRO-TERM_B: J2.2, Q4.5-8, RN3.7 (R2.2)
PYRO-TERM_C: J2.3, Q3.5-8, RN3.6 (R3.2)
PYRO-TERM_D: J2.4, Q2.5-8, RN3.5 (R4.2)
PYRO_A: R11.2, STM1.62 (PB9)
PYRO_B: R10.2, STM1.61 (PB8)
PYRO_C: R9.2, STM1.54 (PD2)
PYRO_D: R8.2, STM1.53 (PC12)
RFD_900: ESP1.37 (IO41), R57.2
RFM95W_ANT: ANT1.1, RFM1.9 (ANT)
RFM95W_DI0: ESP1.18 (IO14), RFM1.14 (DIO0)
RFM95W_DI1: RFM1.15 (DIO1), RFM2.5
RFM95W_DI2: RFM1.16 (DIO2), RFM2.4
RFM95W_DI3: RFM1.11 (DIO3), RFM2.3
RFM95W_DI4: RFM1.12 (DIO4), RFM2.2
RFM95W_DI5: RFM1.7 (DIO5), RFM2.1
RFM95W_RST: ESP1.13 (IO9), RFM1.6 (RESET)
SD_CS: SD1.2 (CD/DAT3), STM1.38 (PC7)
SPI-1_ESP32: ESP1.38 (IO42), R56.2
SPI-1_STM32: ESP1.39 (TXD0), R55.2
SPI-2_STM32: ESP1.40 (RXD0), R54.2
STM32-BOOT0: R4.2, R5.1, RST-BOOT-STM1.1, STM1.60 (BOOT0)
STM32-HSE_IN: C8.2, HSE1.1, STM1.5 (PH0)
STM32-HSE_OUT: R3.1, STM1.6 (PH1)
STM32-I2C2_SCL: I2C-STM1.4, R36.1, STM1.29 (PB10)
STM32-I2C2_SDA: I2C-STM1.3, R35.1, STM1.30 (PB11)
STM32-NRST: C12.1, RST-BOOT-STM1.3, S4.2, STM1.7 (NRST), SWD1.10
STM32-RGB_IN: RGB1.4 (DIN), STM1.2 (PC13)
STM32-SWCLK: STM1.49 (PA14), SWD1.4
STM32-SWDIO: STM1.46 (PA13), SWD1.2
STM32-UART1_RX: STM1.43 (PA10), UART1-RFD-STM1.3
STM32-UART1_TX: STM1.42 (PA9), UART1-RFD-STM1.4
STM32-UART2_RX: STM1.17 (PA3), UART2-STM1.3
STM32-UART2_TX: STM1.16 (PA2), UART2-STM1.4
STM32-UART3_RX: R18.1, STM1.52 (PC11)
STM32-UART3_TX: R19.1, STM1.51 (PC10)
STM32_USB_D+: STM1.45 (PA12), U1.4 (I/O2)
STM32_USB_D-: STM1.44 (PA11), U1.6 (I/O1)
USB1_D+: U1.3 (I/O2), USB1.A6 (D+), USB1.B6 (D+)
USB1_D-: U1.1 (I/O1), USB1.A7 (D-), USB1.B7 (D-)
USB2_D+: U2.3 (I/O2), USB2.A6 (D+), USB2.B6 (D+)
USB2_D-: U2.1 (I/O1), USB2.A7 (D-), USB2.B7 (D-)
V-TERM_A: RN2.8 (R1.2), RN3.1 (R1.1), STM1.8 (PC0)
V-TERM_B: RN2.7 (R2.2), RN3.2 (R2.1), STM1.9 (PC1)
V-TERM_C: RN2.6 (R3.2), RN3.3 (R3.1), STM1.10 (PC2)
V-TERM_D: RN2.5 (R4.2), RN3.4 (R4.1), STM1.11 (PC3)
VBUS: D5.A, Q6.2 (B), R47.1, U1.5 (VBUS), U2.5 (VBUS), USB1.A4 (VBUS), USB1.A9 (VBUS), USB1.B4 (VBUS), USB1.B9 (VBUS), USB2.A4 (VBUS), USB2.A9 (VBUS), USB2.B4 (VBUS), USB2.B9 (VBUS)
VIN: C32.1, C33.1, C34.1, C35.1, D5.C, Q6.3 (E), R41.1, R42.1, U10.3 (VIN), U11.3 (VIN)

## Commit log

2023-07-17 Backlink to CADLAB.io has been added.
2023-07-17 initial file upload
2023-08-02 Added Power & USB
2023-08-03 Added IMUs and Barometers
2023-08-09 Added ESP32 + Modified Symbols
2023-08-11 added hierarchal sheets
2023-08-11 Organized Schematics & Fixed Notes
2023-08-11 deleted files
2023-08-11 Added OSH Logo
2023-08-12 Updated files
2023-09-20 Added INA219
2023-09-28 Added connectors
2023-10-26 updated footprint library
2023-10-28 Updated symbol footprints
2023-12-02 updated schematic
2023-12-02 updated pcb
2023-12-03 grouped components
2023-12-31 updated tracks
2024-03-03 started routing
2024-03-07 more routing
2024-05-22 significant amount of routing done
2024-05-24 signals routed
2024-05-24 updated read me
2024-05-24 updated schematics
2024-05-27 added power planes
2024-05-29 updated aether image
2024-05-29 moved pcb files to hardware folder
2024-05-29 updated image
2024-05-29 Reorganizing directory
2024-05-29 create hardware folder
2025-02-03 added BNO086
2025-03-31 rev2 component placement
2025-07-07 rev2 routed
2025-07-12 updated routing
2025-07-18 Updated minimum via hole size to 0.3mm.
